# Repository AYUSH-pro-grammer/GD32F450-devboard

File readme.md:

# GD32F450 Custom Dev Board

Custom development board using the GD32F450ZGT6 ARM Cortex-M4 microcontroller.

Designed to provide a custom hardware platform that includes the microcontroller, external memory, storage, power management and expansion.

External SDRAM, W25Q128JVE SPI flash, microSD card, USB-C, FPC connections, and GPIO expansion are available.

This repo contains the hardware design files, KiCad project, PCB layout, manufacture Gerber files, components BOM and 3D model.

## Why This Project?

To understand more than just development boards and how to make one.

I had chosen to actually design a complete development board around the GD32F450ZGT6. This involved going through the whole design process for the hardware, including schematic design, component selection, PCB layout, 4-layer routing, and manufacturing file design.

This would allow me to design a flexible development platform and gain practical knowledge of embedded hardware design, memory inclusion, power management, PCB design, and hardware manufacturing.

Most importantly it allowed me to take a microcontroller data sheet and an idea and produce a complete PCB that can be manufactured.

## Inspiration

The inspiration for my project was to create a development board that combines the flexibility of a general purpose microcontroller with an advanced embedded system.

This would allow me to experiment with adding external memory and storage along with multiple expansion ports to my microcontroller.

I wanted to keep the design simple so that I had a useful board to experiment, learn and use for future embedded projects.

All components were selected to help me understand how each hardware block interacts together.

## Hardware

The board contains several hardware components that work together to form an embedded development platform.

| Feature | Description |
|---|---|
| **Microcontroller** | GD32F450ZGT6 ARM Cortex-M4 |
| **External SDRAM** | TSOP-II-54 SDRAM interface |
| **SPI Flash** | W25Q128JVE 128-Mbit serial flash |
| **Power Management** | AP63203WU buck regulator |
| **USB Connectivity** | USB Type-C receptacle |
| **Removable Storage** | microSD card interface |
| **FPC Interfaces** | Two 40-pin, 0.5 mm-pitch connectors |
| **Expansion Headers** | Two 40-pin headers and one 8-pin header |
| **PCB Stackup** | Four-layer PCB with dedicated internal power and ground planes |

The board also includes supporting circuitry for clock generation, reset, power filtering and user interaction.

External memory, removable storage and expansion interfaces provide flexibility for a range of embedded development experiments.

## Project Images

### 3D PCB Design

The PCB was designed and visualized in KiCad's 3D Viewer to inspect component placement, board layout, and both sides of the design.

**Front View**

**Back View**

### PCB Layout and Routing

**PCB Routing**

**PCB Routing Without Copper Fill**

### Circuit Schematic

The schematic shows the electrical design and the connections between the microcontroller, memory, power circuitry, and peripheral interfaces.

## Bill of Materials (BOM)

The complete component-level BOM is available in [`bom.csv`](bom.csv). 

| Component Name | Quantity | Price (USD) | Purchase Link |
|---|---:|---:|---|
| 100nF Capacitor | 23 | $0.1058 | [LCSC](https://www.lcsc.com/product-detail/C1525.html) |
| 10pF Capacitor | 2 | $0.0104 | [LCSC](https://www.lcsc.com/product-detail/C3860506.html) |
| 22pF Capacitor | 2 | $0.0086 | [LCSC](https://www.lcsc.com/product-detail/C1555.html) |
| 10uF Capacitor | 2 | $0.0270 | [LCSC](https://www.lcsc.com/product-detail/C163694.html) |
| 22uF Capacitor | 2 | $0.1144 | [LCSC](https://www.lcsc.com/product-detail/C109448.html) |
| Dual Schottky Diode | 2 | $0.0370 | [LCSC](https://www.lcsc.com/product-detail/C545547.html) |
| TVS Diode | 2 | $0.0324 | [LCSC](https://www.lcsc.com/product-detail/C266458.html) |
| 5V TVS Diode | 2 | $0.0824 | [LCSC](https://www.lcsc.com/product-detail/C260407.html) |
| Green LED | 5 | $0.0730 | [LCSC](https://www.lcsc.com/product-detail/C20608784.html) |
| Resettable Fuse | 1 | $0.0458 | [LCSC](https://www.lcsc.com/product-detail/C210357.html) |
| 40-pin FPC Connector | 1 | $0.1940 | [LCSC](https://www.lcsc.com/product-detail/C7419877.html) |
| 40-pin FPC Connector | 1 | $0.3856 | [LCSC](https://www.lcsc.com/product-detail/C202114.html) |
| microSD Card Connector | 1 | $1.7896 | [LCSC](https://www.lcsc.com/product-detail/C114218.html) |
| USB-C Receptacle | 1 | $0.1724 | [LCSC](https://www.lcsc.com/product-detail/C165948.html) |
| 8-pin Header | 1 | $0.0320 | [LCSC](https://www.lcsc.com/product-detail/C5156616.html) |
| 40-pin Dual-row Header | 2 | $0.4286 | [LCSC](https://www.lcsc.com/product-detail/C50980.html) |
| 2.2uH Inductor | 1 | $0.1495 | [LCSC](https://www.lcsc.com/product-detail/C576403.html) |
| 1MΩ Resistor | 1 | $0.0026 | [LCSC](https://www.lcsc.com/product-detail/C26083.html) |
| 10kΩ Resistor | 11 | $0.0341 | [LCSC](https://www.lcsc.com/product-detail/C25744.html) |
| 5.1kΩ Resistor | 2 | $0.0052 | [LCSC](https://www.lcsc.com/product-detail/C25905.html) |
| 450kΩ Resistor | 1 | $0.0026 | [LCSC](https://www.lcsc.com/product-detail/C25883.html) |
| 100kΩ Resistor | 1 | $0.0013 | [LCSC](https://www.lcsc.com/product-detail/C25741.html) |
| 4.7kΩ Resistor | 5 | $0.0145 | [LCSC](https://www.lcsc.com/product-detail/C25900.html) |
| Tactile Push-button Switch | 3 | $1.7496 | [LCSC](https://www.lcsc.com/product-detail/C116501.html) |
| 256Mbit SDRAM | 1 | $6.1612 | [LCSC](https://www.lcsc.com/product-detail/C62246.html) |
| GD32F450ZGT6 Microcontroller | 1 | $7.2594 | [LCSC](https://www.lcsc.com/product-detail/C99163.html) |
| W25Q128JVE SPI Flash | 1 | $3.8086 | [LCSC](https://www.lcsc.com/product-detail/C2456297.html) |
| AP63203WU Buck Regulator | 1 | $0.7925 | [LCSC](https://www.lcsc.com/product-detail/C780769.html) |
| 32.768kHz Crystal | 1 | $0.1329 | [LCSC](https://www.lcsc.com/product-detail/C271654.html) |
| 25MHz Crystal | 1 | $0.0936 | [LCSC](https://www.lcsc.com/product-detail/C7301943.html) |
| **Component Subtotal** | | **$23.7466** | |
| PCB Fabrication – JLCPCB (4-layer) | 1 | $30.00 | [JLCPCB](https://jlcpcb.com/) |
| **Grand Total** | | **$53.7466** | |

### Firmware Flashing

The firmware is written in C using the GD32F4xx Standard Peripheral Library. To build it, install the ARM GNU Toolchain and add the required GD32F4xx library, startup files and linker script. Once compiled, generate a firmware image and flash it to the GD32F450ZGT6 using an SWD programmer such as a J-Link or CMSIS-DAP debugger. After flashing, connect to USART0 through PA9 (TX) and PA10 (RX) using a serial terminal configured for 115200 baud, 8-N-1. The initial firmware provides basic MCU information, an internal SRAM test, uptime reporting and a serial command interface. External SDRAM, SPI flash, microSD and USB drivers are not yet implemented.

## Manufacturing

We have now designed our PCB and can produce our manufacturing files from KiCad.

The gerber/ folder contains all the Gerber and drill files needed to manufacture a PCB. This has also been zipped together to make it easier to upload.

These files are:

Copper Layers: Front, Back, In1, In2

Solder Mask: Front, Back

Paste Layers: Front, Back

Silkscreen: Front, Back

Board Outline: Edge.Cuts

Drills: Plated (PTH), Non-Plated (NPTH)

Gerber File:

Layer and Fabrication Information

## PCB Manufacture

Our board has been designed as a 4 layer PCB. We can manufacture our board using [JLCPCB](https://jlcpcb.com/).

The cost of manufacturing our PCB is estimated to be $30 USD.

To manufacture our board we need to upload our gerber.zip file to the Gerber viewer on the PCB manufacturers website. Check the layers and board outline are detected correctly and the settings for manufacture are correct before ordering.

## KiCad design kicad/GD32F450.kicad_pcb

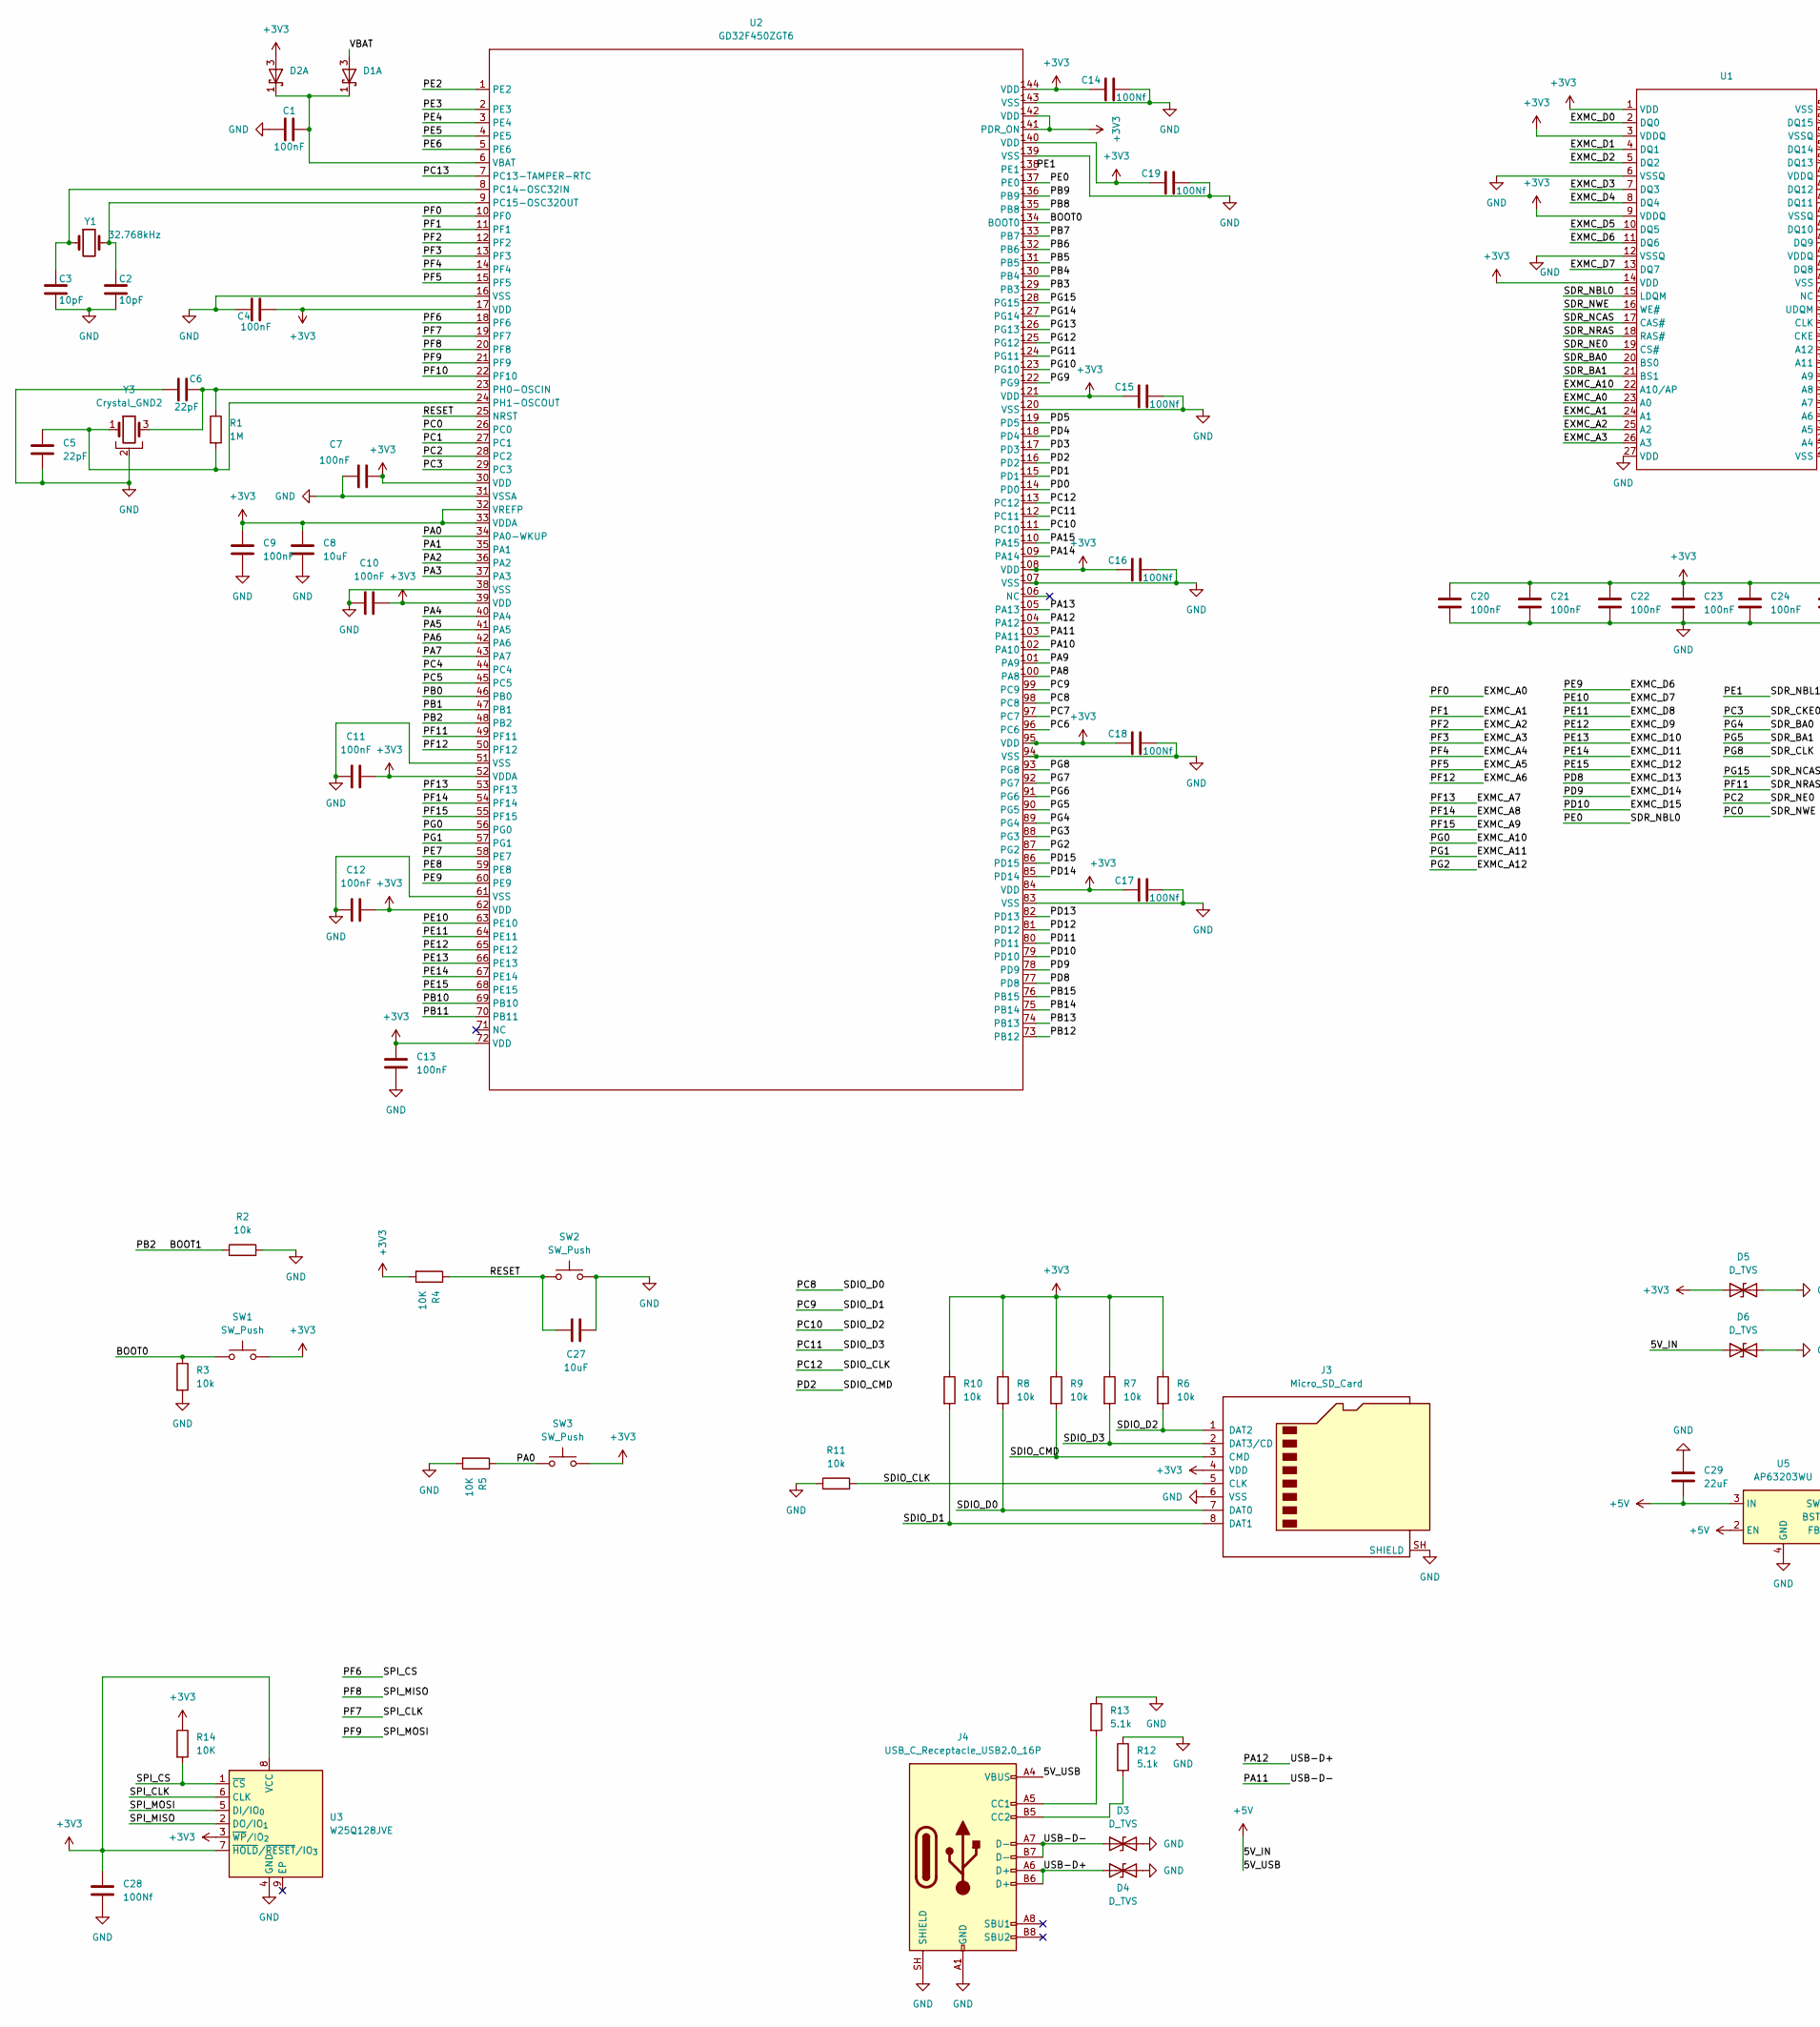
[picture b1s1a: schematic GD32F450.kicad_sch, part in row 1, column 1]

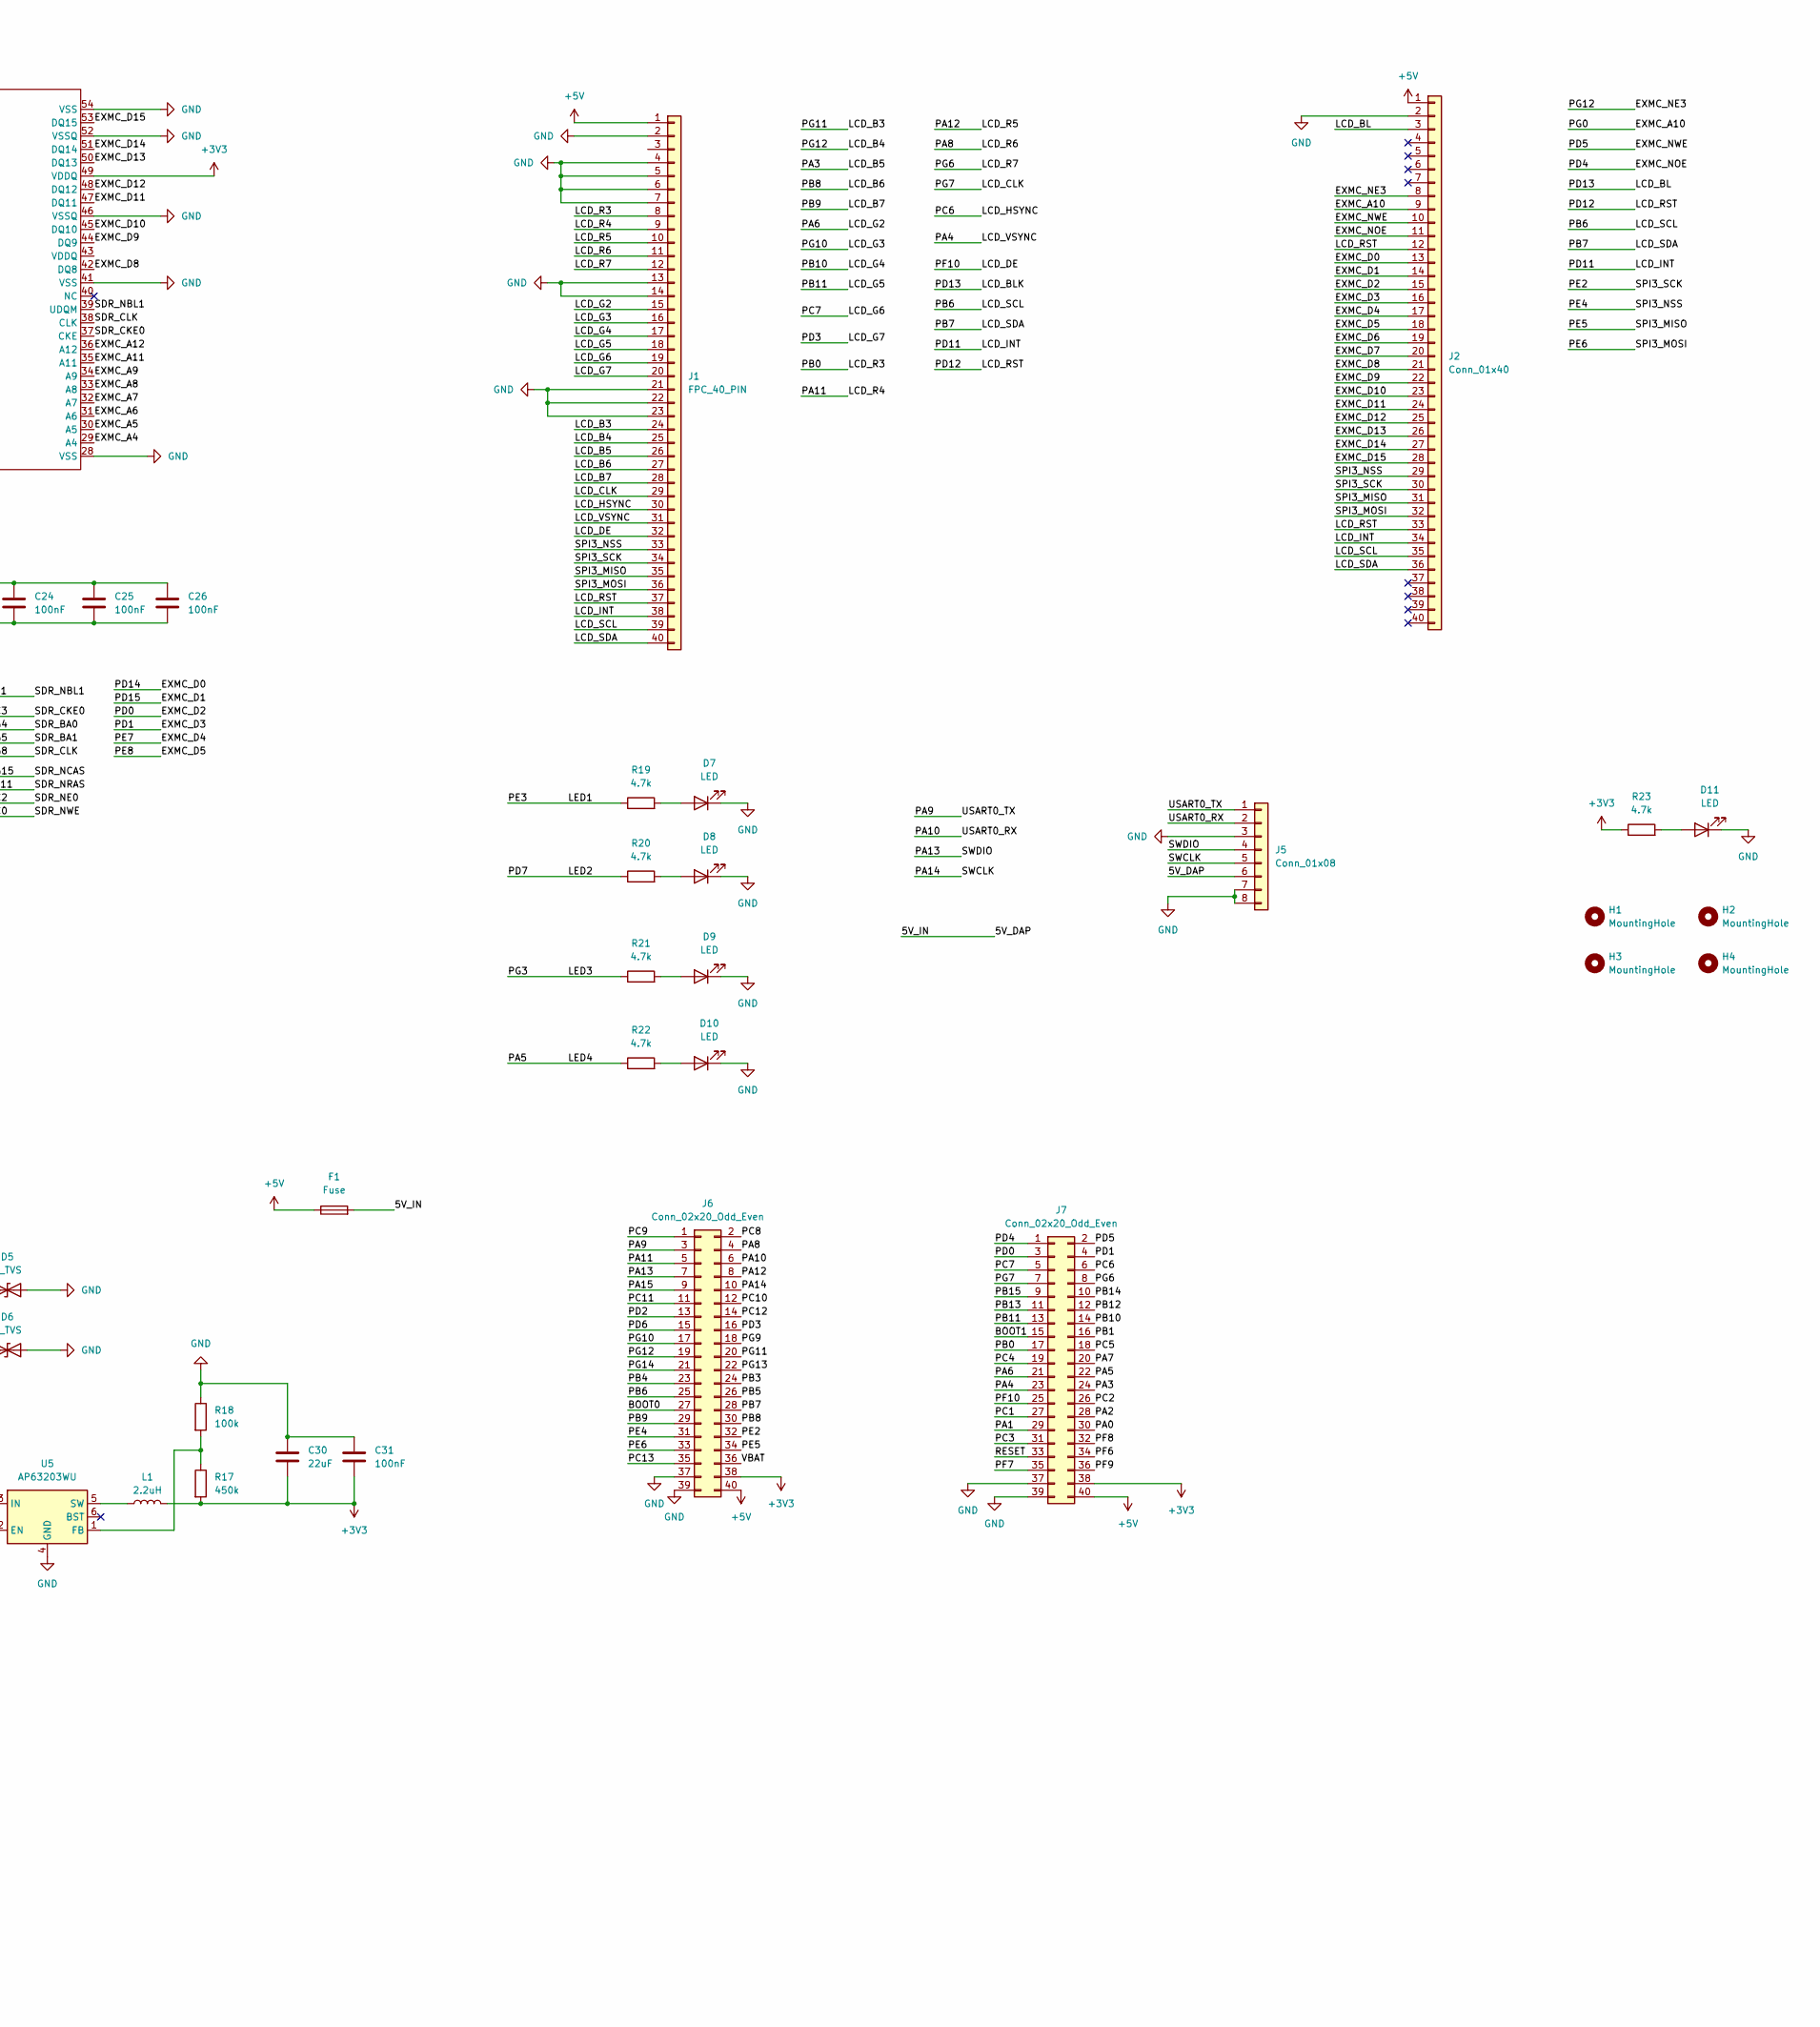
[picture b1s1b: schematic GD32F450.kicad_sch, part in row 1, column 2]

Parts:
C1, C4, C7, C9, C10, C11, C12, C13, C20, C21, C22, C23, C24, C25, C26, C31: 100nF; C_0402_1005Metric
C2, C3: 10pF; C_0402_1005Metric
C5, C6: 22pF; C_0402_1005Metric
C8, C27: 10uF; C_0402_1005Metric
C14, C15, C16, C17, C18, C19, C28: 100Nf; C_0402_1005Metric
C29, C30: 22uF; C_0603_1608Metric
D1, D2: D_Schottky_Dual_CommonAnode_KKA_Split; SOT-523
D3, D4: D_TVS; D_SOD-882
D5, D6: D_TVS; D_SMB
D7, D8, D9, D10, D11: LED; LED_0402_1005Metric
F1: Fuse; Fuse_0603_1608Metric
H1, H2, H3, H4: MountingHole; MountingHole_3.2mm_M3
J1: FPC_40_PIN; Amphenol_F32Q-1A7x1-11040_1x40-1MP_P0.5mm_Horizontal
J2: Conn_01x40; Hirose_FH12-40S-0.5SH_1x40-1MP_P0.50mm_Horizontal
J3: Micro_SD_Card; microSD_HC_Hirose_DM3AT-SF-PEJM5
J4: USB_C_Receptacle_USB2.0_16P; USB_C_Receptacle_HRO_TYPE-C-31-M-12
J5: Conn_01x08; PinHeader_1x08_P2.54mm_Vertical
J6, J7: Conn_02x20_Odd_Even; PinHeader_2x20_P2.54mm_Vertical
L1: 2.2uH; L_1008_2520Metric
R1: 1M; R_0402_1005Metric
R2, R3, R6, R7, R8, R9, R10, R11: 10k; R_0402_1005Metric
R4, R5, R14: 10K; R_0402_1005Metric
R12, R13: 5.1k; R_0402_1005Metric
R17: 450k; R_0402_1005Metric
R18: 100k; R_0402_1005Metric
R19, R20, R21, R22, R23: 4.7k; R_0402_1005Metric
SW1, SW2, SW3: SW_Push; SW_SPST_PTS810
U1: TSOP-II-54_22.2x10.16mm_P0.8mm
U2: GD32F450ZGT6; GD32F450ZGT6_LQFP144_20x20mm_P0.5mm
U3: W25Q128JVE; WSON-8-1EP_8x6mm_P1.27mm_EP3.4x4.3mm
U5: AP63203WU; TSOT-23-6
Y1: 32.768kHz; Crystal_SMD_3215-2Pin_3.2x1.5mm
Y3: Crystal_GND2; Crystal_SMD_2016-4Pin_2.0x1.6mm

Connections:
+3V3: C4.2, C7.2, C8.1, C9.1, C10.2, C11.2, C12.2, C13.1, C14.1, C15.1, C16.1, C17.1, C18.1, C19.1, C20.1, C21.1, C22.1, C23.1, C24.1, C25.1, C26.1, C28.1, C30.2, C31.2, D2.3 (A), D5.1 (A1), J3.4 (VDD), J6.38, J7.38, L1.2, R4.2, R6.1, R7.1, R8.1, R9.1, R10.1, R14.1, R17.2, R23.1, SW1.2, SW3.2, U1.1 (VDD), U1.3 (VDDQ), U1.9 (VDDQ), U1.14 (VDD), U1.49 (VDDQ), U2.17 (VDD), U2.30 (VDD), U2.32 (VREFP), U2.33 (VDDA), U2.39 (VDD), U2.52 (VDDA), U2.62 (VDD), U2.72 (VDD), U2.84 (VDD), U2.95 (VDD), U2.108 (VDD), U2.121 (VDD), U2.140 (VDD), U2.141 (PDR_ON), U2.142 (VDD), U2.144 (VDD), U3.3 (~WP/IO_{2}), U3.7 (~HOLD/~RESET/IO_{3}), U3.8 (VCC)
+5V: C29.2, D6.1 (A1), F1.1, F1.2, J1.1, J2.1, J4.A4 (VBUS), J4.A9 (VBUS), J4.B4 (VBUS), J4.B9 (VBUS), J5.6, J6.40, J7.40, U5.2 (EN), U5.3 (IN)
/BOOT0: J6.27, R3.1, SW1.1, U2.134 (BOOT0)
/BOOT1: J7.15, R2.1, U2.48 (PB2)
/EXMC_A0: U1.23 (A0), U2.10 (PF0)
/EXMC_A1: U1.24 (A1), U2.11 (PF1)
/EXMC_A2: U1.25 (A2), U2.12 (PF2)
/EXMC_A3: U1.26 (A3), U2.13 (PF3)
/EXMC_A4: U1.29 (A4), U2.14 (PF4)
/EXMC_A5: U1.30 (A5), U2.15 (PF5)
/EXMC_A6: U1.31 (A6), U2.50 (PF12)
/EXMC_A7: U1.32 (A7), U2.53 (PF13)
/EXMC_A8: U1.33 (A8), U2.54 (PF14)
/EXMC_A9: U1.34 (A9), U2.55 (PF15)
/EXMC_A10: J2.9, U1.22 (A10/AP), U2.56 (PG0)
/EXMC_A11: U1.35 (A11), U2.57 (PG1)
/EXMC_A12: U1.36 (A12), U2.87 (PG2)
/EXMC_D0: J2.13, U1.2 (DQ0), U2.85 (PD14)
/EXMC_D1: J2.14, U1.4 (DQ1), U2.86 (PD15)
/EXMC_D2: J2.15, J7.3, U1.5 (DQ2), U2.114 (PD0)
/EXMC_D3: J2.16, J7.4, U1.7 (DQ3), U2.115 (PD1)
/EXMC_D4: J2.17, U1.8 (DQ4), U2.58 (PE7)
/EXMC_D5: J2.18, U1.10 (DQ5), U2.59 (PE8)
/EXMC_D6: J2.19, U1.11 (DQ6), U2.60 (PE9)
/EXMC_D7: J2.20, U1.13 (DQ7), U2.63 (PE10)
/EXMC_D8: J2.21, U1.42 (DQ8), U2.64 (PE11)
/EXMC_D9: J2.22, U1.44 (DQ9), U2.65 (PE12)
/EXMC_D10: J2.23, U1.45 (DQ10), U2.66 (PE13)
/EXMC_D11: J2.24, U1.47 (DQ11), U2.67 (PE14)
/EXMC_D12: J2.25, U1.48 (DQ12), U2.68 (PE15)
/EXMC_D13: J2.26, U1.50 (DQ13), U2.77 (PD8)
/EXMC_D14: J2.27, U1.51 (DQ14), U2.78 (PD9)
/EXMC_D15: J2.28, U1.53 (DQ15), U2.79 (PD10)
/EXMC_NE3: J1.25, J2.8, J6.19, U2.125 (PG12)
/EXMC_NOE: J2.11, J7.1, U2.118 (PD4)
/EXMC_NWE: J2.10, J7.2, U2.119 (PD5)
/LCD_B3: J1.24, J6.20, U2.124 (PG11)
/LCD_B5: J1.26, J7.24, U2.37 (PA3)
/LCD_B6: J1.27, J6.30, U2.135 (PB8)
/LCD_B7: J1.28, J6.29, U2.136 (PB9)
/LCD_BL: J2.3, U2.82 (PD13)
/LCD_CLK: J1.29, J7.7, U2.92 (PG7)
/LCD_DE: J1.32, J7.25, U2.22 (PF10)
/LCD_G2: J1.15, J7.21, U2.42 (PA6)
/LCD_G3: J1.16, J6.17, U2.123 (PG10)
/LCD_G4: J1.17, J7.14, U2.69 (PB10)
/LCD_G5: J1.18, J7.13, U2.70 (PB11)
/LCD_G6: J1.19, J7.5, U2.97 (PC7)
/LCD_G7: J1.20, J6.16, U2.117 (PD3)
/LCD_HSYNC: J1.30, J7.6, U2.96 (PC6)
/LCD_INT: J1.38, J2.34, U2.80 (PD11)
/LCD_R3: J1.8, J7.17, U2.46 (PB0)
/LCD_R4: D3.1 (A1), J1.9, J4.A7 (D-), J4.B7 (D-), J6.5, U2.103 (PA11)
/LCD_R5: D4.1 (A1), J1.10, J4.A6 (D+), J4.B6 (D+), J6.8, U2.104 (PA12)
/LCD_R6: J1.11, J6.4, U2.100 (PA8)
/LCD_R7: J1.12, J7.8, U2.91 (PG6)
/LCD_RST: J1.37, J2.12, J2.33, U2.81 (PD12)
/LCD_SCL: J1.39, J2.35, J6.25, U2.132 (PB6)
/LCD_SDA: J1.40, J2.36, J6.28, U2.133 (PB7)
/LCD_VSYNC: J1.31, J7.23, U2.40 (PA4)
/LED1: R19.1, U2.2 (PE3)
/LED2: R20.1
/LED3: R21.1, U2.88 (PG3)
/LED4: J7.22, R22.1, U2.41 (PA5)
/PA0: J7.30, R5.1, SW3.1, U2.34 (PA0-WKUP)
/PA1: J7.29, U2.35 (PA1)
/PA2: J7.28, U2.36 (PA2)
/PA7: J7.20, U2.43 (PA7)
/PA9: J5.1, J6.3, U2.101 (PA9)
/PA10: J5.2, J6.6, U2.102 (PA10)
/PA13: J5.4, J6.7, U2.105 (PA13)
/PA14: J5.5, J6.10, U2.109 (PA14)
/PA15: J6.9, U2.110 (PA15)
/PB1: J7.16, U2.47 (PB1)
/PB3: J6.24, U2.129 (PB3)
/PB4: J6.23, U2.130 (PB4)
/PB5: J6.26, U2.131 (PB5)
/PB12: J7.12, U2.73 (PB12)
/PB13: J7.11, U2.74 (PB13)
/PB14: J7.10, U2.75 (PB14)
/PB15: J7.9, U2.76 (PB15)
/PC0: U1.16 (WE#), U2.26 (PC0)
/PC1: J7.27, U2.27 (PC1)
/PC2: J7.26, U1.19 (CS#), U2.28 (PC2)
/PC3: J7.31, U1.37 (CKE), U2.29 (PC3)
/PC4: J7.19, U2.44 (PC4)
/PC5: J7.18, U2.45 (PC5)
/PC8: J3.7 (DAT0), J6.2, R8.2, U2.98 (PC8)
/PC9: J3.8 (DAT1), J6.1, R10.2, U2.99 (PC9)
/PC10: J3.1 (DAT2), J6.12, R6.2, U2.111 (PC10)
/PC11: J3.2 (DAT3/CD), J6.11, R7.2, U2.112 (PC11)
/PC12: J3.5 (CLK), J6.14, R11.2, U2.113 (PC12)
/PC13: J6.35, U2.7 (PC13-TAMPER-RTC)
/PD2: J3.3 (CMD), J6.13, R9.2, U2.116 (PD2)
/PD6: J6.15
/PE0: U1.15 (LDQM), U2.137 (PE0)
/PE1: U1.39 (UDQM), U2.138 (PE1)
/PE2: J1.34, J2.30, J6.32, U2.1 (PE2)
/PE4: J1.33, J2.29, J6.31, U2.3 (PE4)
/PE5: J1.35, J2.31, J6.34, U2.4 (PE5)
/PE6: J1.36, J2.32, J6.33, U2.5 (PE6)
/PF6: J7.34, R14.2, U2.18 (PF6), U3.1 (~CS)
/PF7: J7.35, U2.19 (PF7), U3.6 (CLK)
/PF8: J7.32, U2.20 (PF8), U3.2 (DO/IO_{1})
/PF9: J7.36, U2.21 (PF9), U3.5 (DI/IO_{0})
/PF11: U1.18 (RAS#), U2.49 (PF11)
/PG4: U1.20 (BS0), U2.89 (PG4)
/PG5: U1.21 (BS1), U2.90 (PG5)
/PG8: U1.38 (CLK), U2.93 (PG8)
/PG9: J6.18, U2.122 (PG9)
/PG13: J6.22, U2.126 (PG13)
/PG14: J6.21, U2.127 (PG14)
/PG15: U1.17 (CAS#), U2.128 (PG15)
/RESET: C27.1, J7.33, R4.1, SW2.1, U2.25 (NRST)
/VBAT: D1.3 (A), J6.36
GND: C1.2, C2.2, C3.2, C4.1, C5.2, C6.2, C7.1, C8.2, C9.2, C10.1, C11.1, C12.1, C13.2, C14.2, C15.2, C16.2, C17.2, C18.2, C19.2, C20.2, C21.2, C22.2, C23.2, C24.2, C25.2, C26.2, C27.2, C28.2, C29.1, C30.1, C31.1, D3.2 (A2), D4.2 (A2), D5.2 (A2), D6.2 (A2), D7.1 (K), D8.1 (K), D9.1 (K), D10.1 (K), D11.1 (K), J1.2, J1.4, J1.5, J1.6, J1.7, J1.13, J1.14, J1.21, J1.22, J1.23, J2.2, J3.6 (VSS), J3.SH (SHIELD), J4.A1 (GND), J4.A12 (GND), J4.B1 (GND), J4.B12 (GND), J4.SH (SHIELD), J5.3, J5.7, J5.8, J6.37, J6.39, J7.37, J7.39, R2.2, R3.2, R5.2, R11.1, R12.1, R13.1, R18.1, SW2.2, U1.6 (VSSQ), U1.12 (VSSQ), U1.27 (VDD), U1.28 (VSS), U1.41 (VSS), U1.46 (VSSQ), U1.52 (VSSQ), U1.54 (VSS), U2.16 (VSS), U2.31 (VSSA), U2.38 (VSS), U2.51 (VSS), U2.61 (VSS), U2.83 (VSS), U2.94 (VSS), U2.107 (VSS), U2.120 (VSS), U2.139 (VSS), U2.143 (VSS), U3.4 (GND), U5.4 (GND), Y3.2
unnamed: C1.1, D1.1 (K), D2.1 (K), U2.6 (VBAT)
unnamed: D7.2 (A), R19.2
unnamed: D8.2 (A), R20.2
unnamed: D9.2 (A), R21.2
unnamed: D10.2 (A), R22.2
unnamed: D11.2 (A), R23.2
unnamed: J4.A5 (CC1), R13.2
unnamed: J4.B5 (CC2), R12.2
unnamed: C3.1, U2.8 (PC14-OSC32IN), Y1.1
unnamed: C2.1, U2.9 (PC15-OSC32OUT), Y1.2
unnamed: C6.1, R1.1, U2.23 (PH0-OSCIN), Y3.3
unnamed: C5.1, R1.2, U2.24 (PH1-OSCOUT), Y3.1
unnamed: R17.1, R18.2, U5.1 (FB)
unnamed: L1.1, U5.5 (SW)

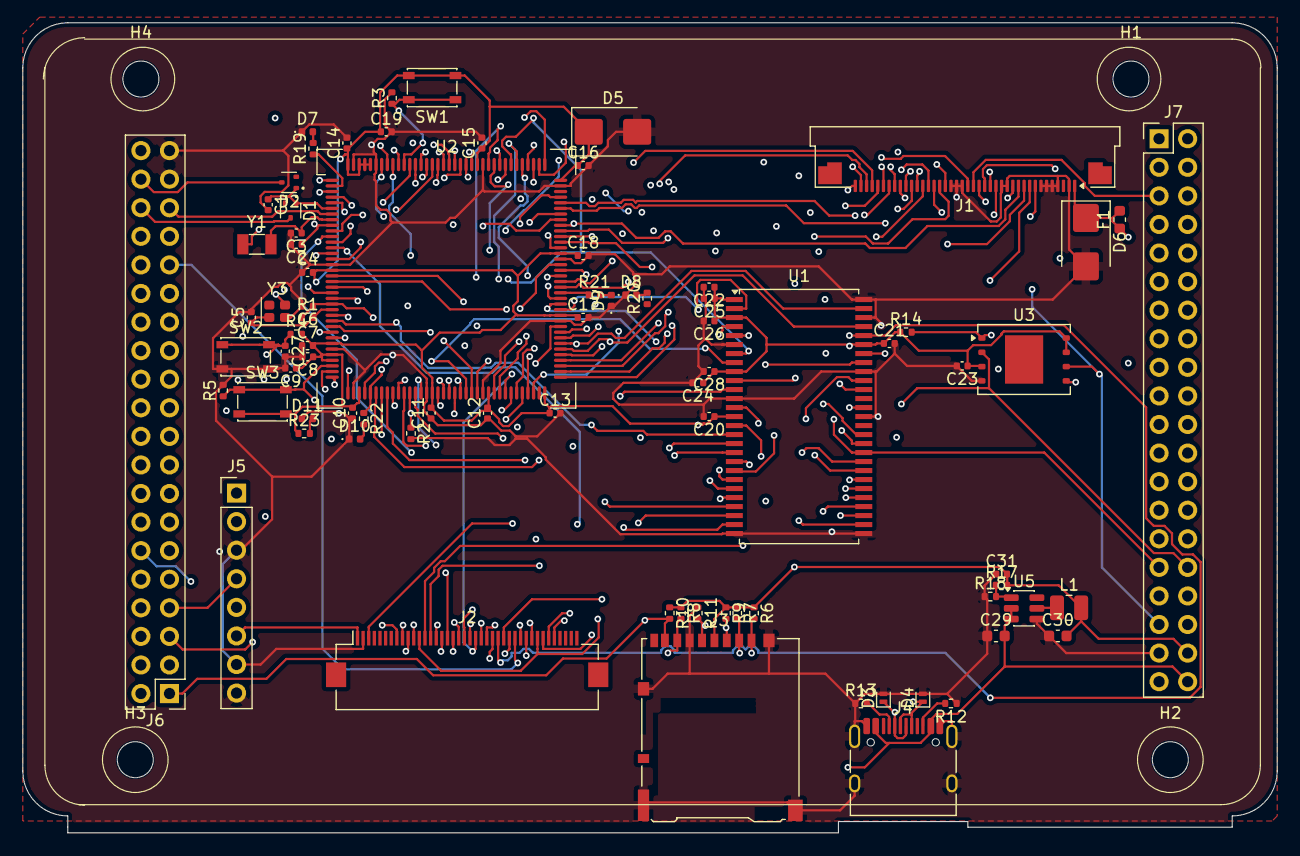
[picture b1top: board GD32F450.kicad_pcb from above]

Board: 4 copper layers, 111.5 x 72.0 mm, 85 parts (0 on the bottom side), 128 nets.

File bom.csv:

"Name","Designator","Quantity","Footprint","LCSC Part Number","Unit Price (USD)","Total Price (USD)","URL"
"100nF capacitor","C1,C4,C7,C9,C10,C11,C12,C13,C20,C21,C22,C23,C24,C25,C26,C31,C14,C15,C16,C17,C18,C19,C28","23","Capacitor_SMD:C_0402_1005Metric","C1525","0.0046","0.1058","https://www.lcsc.com/product-detail/C1525.html"
"10pF capacitor","C2,C3","2","Capacitor_SMD:C_0402_1005Metric","C3860506","0.0052","0.0104","https://www.lcsc.com/product-detail/C3860506.html"
"22pF capacitor","C5,C6","2","Capacitor_SMD:C_0402_1005Metric","C1555","0.0043","0.0086","https://www.lcsc.com/product-detail/C1555.html"
"10uF capacitor","C8,C27","2","Capacitor_SMD:C_0402_1005Metric","C163694","0.0135","0.0270","https://www.lcsc.com/product-detail/C163694.html"
"22uF capacitor","C29,C30","2","Capacitor_SMD:C_0603_1608Metric","C109448","0.0572","0.1144","https://www.lcsc.com/product-detail/C109448.html"
"Dual Schottky diode common anode","D1,D2","2","Package_TO_SOT_SMD:SOT-523","C545547","0.0185","0.0370","https://www.lcsc.com/product-detail/C545547.html"
"TVS diode","D3,D4","2","Diode_SMD:D_SOD-882","C266458","0.0162","0.0324","https://www.lcsc.com/product-detail/C266458.html"
"TVS diode 5V candidate","D5,D6","2","Diode_SMD:D_SMB","C260407","0.0412","0.0824","https://www.lcsc.com/product-detail/C260407.html"
"Green LED","D7,D8,D9,D10,D11","5","LED_SMD:LED_0402_1005Metric","C20608784","0.0146","0.0730","https://www.lcsc.com/product-detail/C20608784.html"
"Resettable fuse 500mA candidate","F1","1","Fuse:Fuse_0603_1608Metric","C210357","0.0458","0.0458","https://www.lcsc.com/product-detail/C210357.html"
"40-pin FPC connector","J1","1","Connector_FFC-FPC:Amphenol_F32Q-1A7x1-11040_1x40-1MP_P0.5mm_Horizontal","C7419877","0.1940","0.1940","https://www.lcsc.com/product-detail/C7419877.html"
"40-pin FPC connector","J2","1","Connector_FFC-FPC:Hirose_FH12-40S-0.5SH_1x40-1MP_P0.50mm_Horizontal","C202114","0.3856","0.3856","https://www.lcsc.com/product-detail/C202114.html"
"MicroSD connector","J3","1","Connector_Card:microSD_HC_Hirose_DM3AT-SF-PEJM5","C114218","1.7896","1.7896","https://www.lcsc.com/product-detail/C114218.html"
"USB-C receptacle","J4","1","Connector_USB:USB_C_Receptacle_HRO_TYPE-C-31-M-12","C165948","0.1724","0.1724","https://www.lcsc.com/product-detail/C165948.html"
"8-pin header","J5","1","Connector_PinHeader_2.54mm:PinHeader_1x08_P2.54mm_Vertical","C5156616","0.0320","0.0320","https://www.lcsc.com/product-detail/C5156616.html"
"40-pin dual-row header","J6,J7","2","Connector_PinHeader_2.54mm:PinHeader_2x20_P2.54mm_Vertical","C50980","0.2143","0.4286","https://www.lcsc.com/product-detail/C50980.html"
"2.2uH inductor","L1","1","Inductor_SMD:L_1008_2520Metric","C576403","0.1495","0.1495","https://www.lcsc.com/product-detail/C576403.html"
"1M resistor","R1","1","Resistor_SMD:R_0402_1005Metric","C26083","0.0026","0.0026","https://www.lcsc.com/product-detail/C26083.html"
"10k resistor","R2,R3,R4,R5,R6,R7,R8,R9,R10,R11,R14","11","Resistor_SMD:R_0402_1005Metric","C25744","0.0031","0.0341","https://www.lcsc.com/product-detail/C25744.html"
"5.1k resistor","R12,R13","2","Resistor_SMD:R_0402_1005Metric","C25905","0.0026","0.0052","https://www.lcsc.com/product-detail/C25905.html"
"450k resistor","R17","1","Resistor_SMD:R_0402_1005Metric","C25883","0.0026","0.0026","https://www.lcsc.com/product-detail/C25883.html"
"100k resistor","R18","1","Resistor_SMD:R_0402_1005Metric","C25741","0.0013","0.0013","https://www.lcsc.com/product-detail/C25741.html"
"4.7k resistor","R19,R20,R21,R22,R23","5","Resistor_SMD:R_0402_1005Metric","C25900","0.0029","0.0145","https://www.lcsc.com/product-detail/C25900.html"
"Tactile push-button switch","SW1,SW2,SW3","3","Button_Switch_SMD:SW_SPST_PTS810","C116501","0.5832","1.7496","https://www.lcsc.com/product-detail/C116501.html"
"256Mbit SDRAM candidate","U1","1","Package_SO:TSOP-II-54_22.2x10.16mm_P0.8mm","C62246","6.1612","6.1612","https://www.lcsc.com/product-detail/C62246.html"
"GD32F450ZGT6 MCU","U2","1","GD32_Liangshanpai.bak:GD32F450ZGT6_LQFP144_20x20mm_P0.5mm","C180076","7.2594","7.2594","https://www.lcsc.com/product-detail/C99163.html"
"W25Q128JVE SPI flash","U3","1","Package_SON:WSON-8-1EP_8x6mm_P1.27mm_EP3.4x4.3mm","C2456297","3.8086","3.8086","https://www.lcsc.com/product-detail/C2456297.html"
"AP63203WU regulator","U5","1","Package_TO_SOT_SMD:TSOT-23-6","C780769","0.7925","0.7925","https://www.lcsc.com/product-detail/C780769.html"
"32.768kHz crystal","Y1","1","Crystal:Crystal_SMD_3215-2Pin_3.2x1.5mm","C271654","0.1329","0.1329","https://www.lcsc.com/product-detail/C271654.html"
"25MHz crystal candidate - verify frequency","Y3","1","Crystal:Crystal_SMD_2016-4Pin_2.0x1.6mm","C7301943","0.0936","0.0936","https://www.lcsc.com/product-detail/C7301943.html"
"Priced component subtotal","","","","","","23.7466",""
"PCB fabrication - JLCPCB","","1","4-layer PCB","","30.00","30.00","https://jlcpcb.com/"
"TOTAL - components plus PCB","","","","","","53.7466",""
